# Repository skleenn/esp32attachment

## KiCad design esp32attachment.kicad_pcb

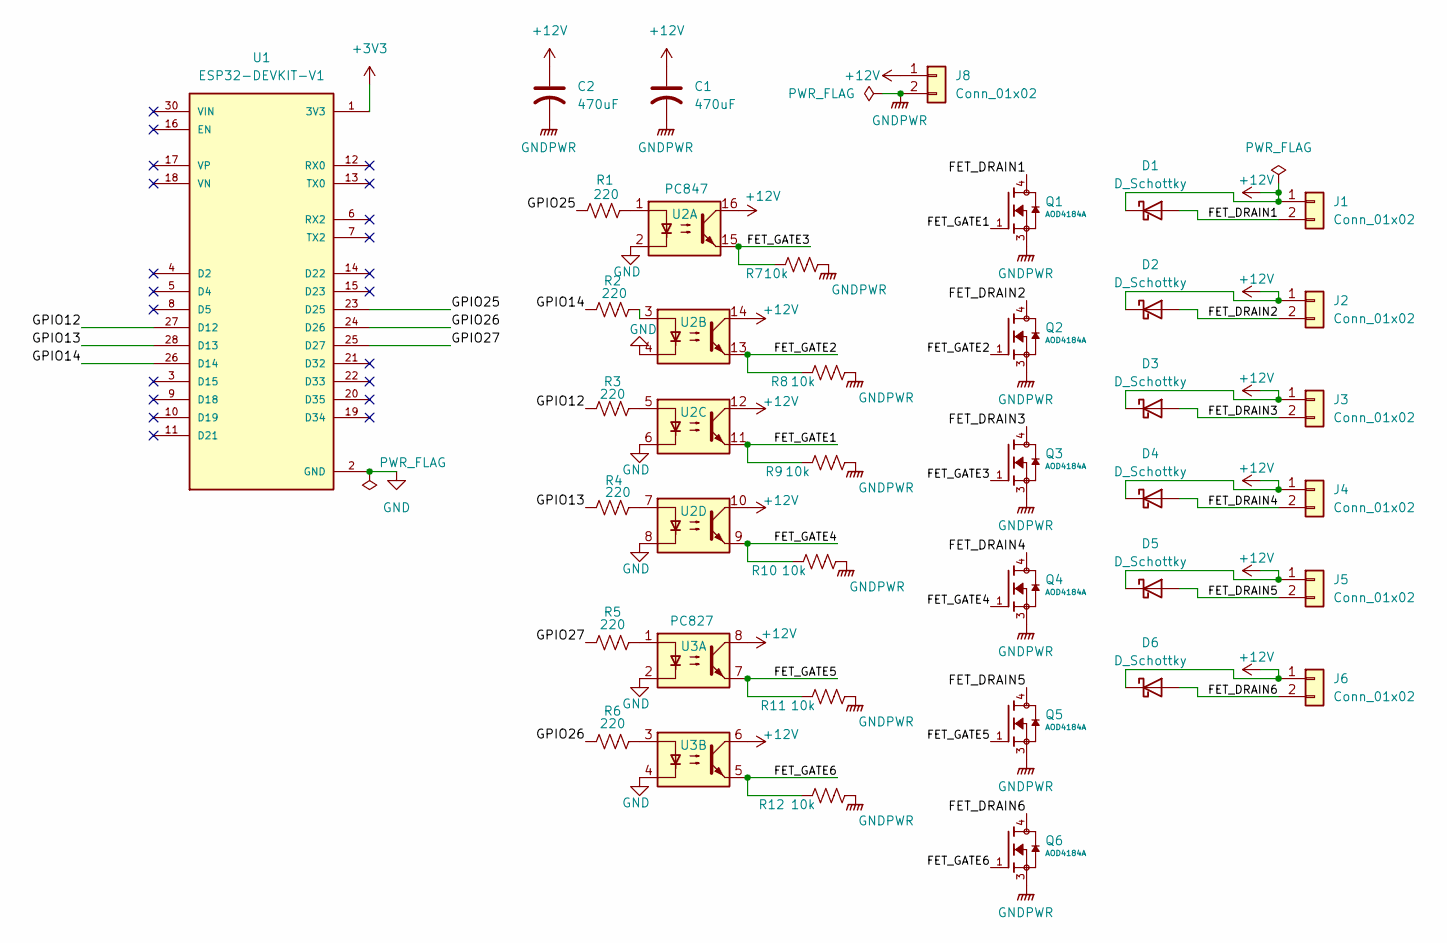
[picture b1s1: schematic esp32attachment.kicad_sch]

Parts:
C1, C2: 470uF; C_Elec_8x10.2
D1, D2, D3, D4, D5, D6: D_Schottky; D_SMC
J1, J2, J3, J4, J5, J6: Conn_01x02; PhoenixContact_SPT_1.5_2-H-3.5_1x02_P3.5mm_Horizontal
J8: Conn_01x02; PhoenixContact_SPT_2.5_2-H-5.0_1x02_P5.0mm_Horizontal
Q1, Q2, Q3, Q4, Q5, Q6: AOD4184A; DPAK228P994X240-4N; PARTREV 0
R1, R2, R3, R4, R5, R6: 220; R_0805_2012Metric_Pad1.20x1.40mm_HandSolder
R7, R8, R9, R10, R11, R12: 10k; R_0805_2012Metric_Pad1.20x1.40mm_HandSolder
U1: ESP32-DEVKIT-V1; MODULE_ESP32_DEVKIT_V1; PARTREV N/A
U2: PC847; DIP-16_W7.62mm
U3: PC827; DIP-8_W7.62mm

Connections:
+3V3: U1.1 (3V3)
+12V: C1.1, C2.1, D1.1 (K), D2.1 (K), D3.1 (K), D4.1 (K), D5.1 (K), D6.1 (K), J1.1, J2.1, J3.1, J4.1, J5.1, J6.1, J8.1, U2.10, U2.12, U2.14, U2.16, U3.6, U3.8
/FET_DRAIN1: D1.2 (A), J1.2, Q1.4
/FET_DRAIN2: D2.2 (A), J2.2, Q2.4
/FET_DRAIN3: D3.2 (A), J3.2, Q3.4
/FET_DRAIN4: D4.2 (A), J4.2, Q4.4
/FET_DRAIN5: D5.2 (A), J5.2, Q5.4
/FET_DRAIN6: D6.2 (A), J6.2, Q6.4
/FET_GATE1: Q1.1, R9.1, U2.11
/FET_GATE2: Q2.1, R8.1, U2.13
/FET_GATE3: Q3.1, R7.1, U2.15
/FET_GATE4: Q4.1, R10.1, U2.9
/FET_GATE5: Q5.1, R11.1, U3.7
/FET_GATE6: Q6.1, R12.1, U3.5
/GPIO12: R3.1, U1.27 (D12)
/GPIO13: R4.1, U1.28 (D13)
/GPIO14: R2.1, U1.26 (D14)
/GPIO25: R1.1, U1.23 (D25)
/GPIO26: R6.1, U1.24 (D26)
/GPIO27: R5.1, U1.25 (D27)
GND: U1.2 (GND), U1.29 (GND), U2.2, U2.4, U2.6, U2.8, U3.2, U3.4
GNDPWR: C1.2, C2.2, J8.2, Q1.3, Q2.3, Q3.3, Q4.3, Q5.3, Q6.3, R7.2, R8.2, R9.2, R10.2, R11.2, R12.2
unnamed: R1.2, U2.1
unnamed: R2.2, U2.3
unnamed: R3.2, U2.5
unnamed: R4.2, U2.7
unnamed: R5.2, U3.1
unnamed: R6.2, U3.3

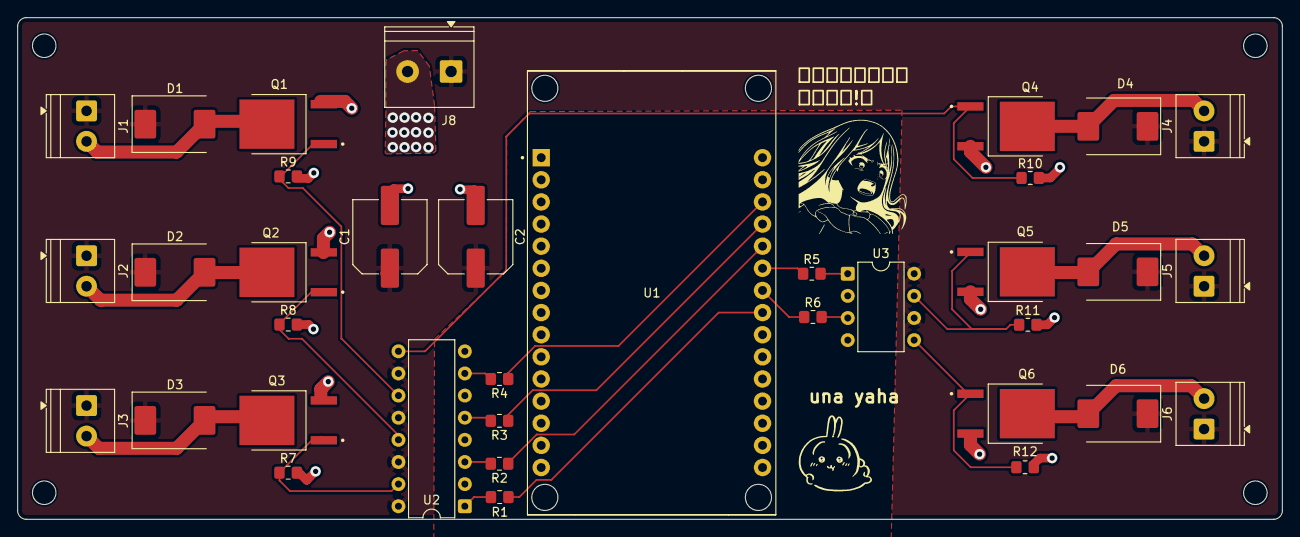
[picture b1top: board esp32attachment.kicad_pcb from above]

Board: 2 copper layers, 145.1 x 57.6 mm, 36 parts (0 on the bottom side), 27 nets.
